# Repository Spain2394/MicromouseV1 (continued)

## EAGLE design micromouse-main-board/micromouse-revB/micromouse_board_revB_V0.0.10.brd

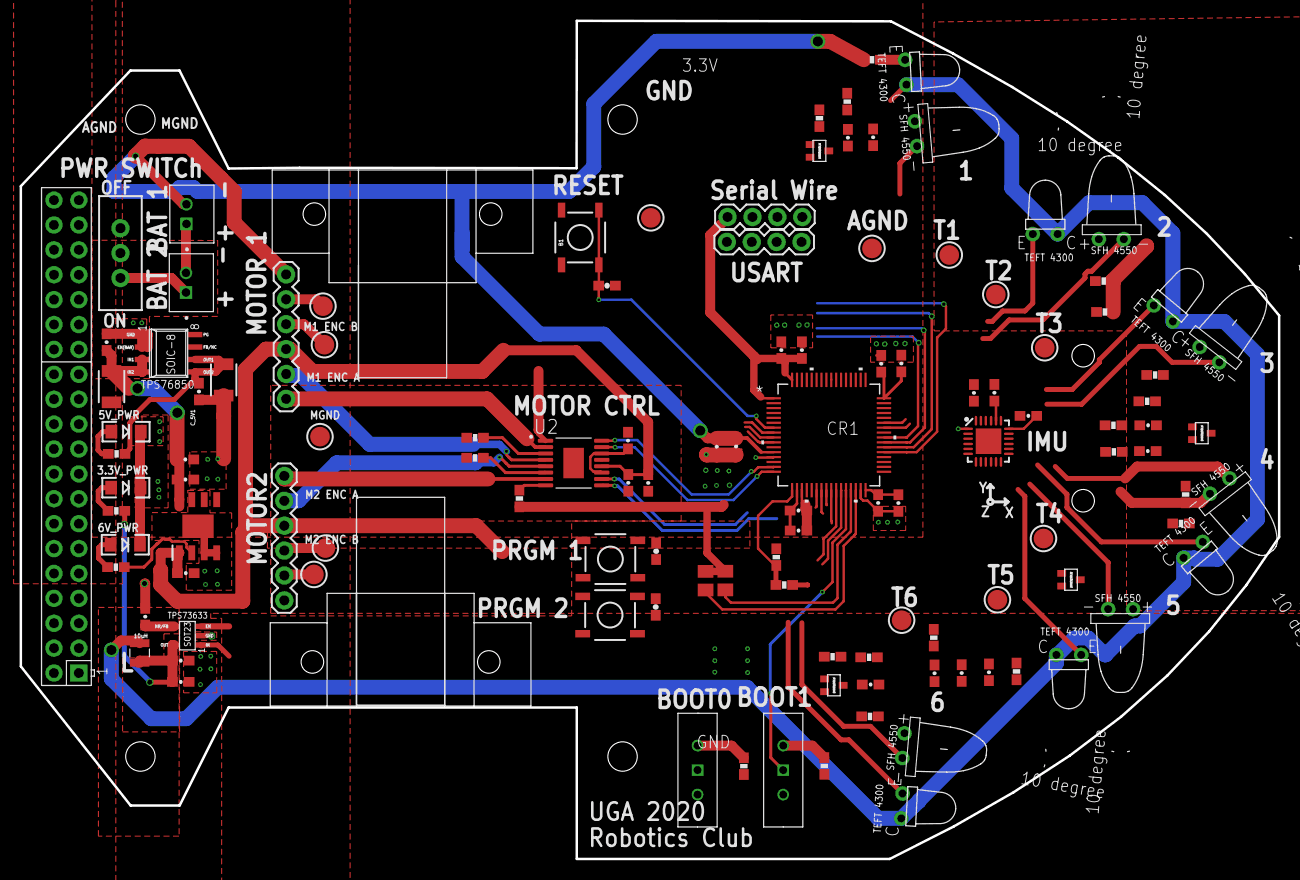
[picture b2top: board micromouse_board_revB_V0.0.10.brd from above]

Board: 2 copper layers, 128.4 x 85.5 mm, 119 parts (0 on the bottom side), 72 nets.

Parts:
3.3V_PWR, 5V_PWR, 6V_PWR: green; LED-1206
B1, B2, B3: TACTILE-SWITCH-SMD
C1: 10nF; 0603-CAP
C2, C18, C21, C23: 4.7uF; 0603-CAP
C4, C7, C17, C22: 0.1uF; 0603-CAP
C8: 1uF; 0603-CAP
CR1: STM32F103RET6; LQFP-64
C_3.3V1, C_3.3V6: 10uF; 0603-CAP
C_3.3V2, C_3.3V7, C_5V1: 0.1uF; 0603-CAP
C_3.3V5: 1uF; 0603-CAP
C_5V2: 47uF; 1210
C_BAT1: 0.1uF; 0603-CAP
C_BAT2: 47uF; 1210
C_D: 0.1uF; 0603-CAP
C_D1: 10uF; 0603-CAP
C_D2: 2.2uF; 0603-CAP
C_ELF1: 4.7uF; 0603-CAP
C_ELF2: 0.1uF; 0603-CAP
C_EM_D1: 4.7uF; 0603-CAP
C_EM_D2: 0.1uF; 0603-CAP
C_ERF1: 4.7uF; 0603-CAP
C_ERF2: 0.1uF; 0603-CAP
C_E_H1: 4.7uF; 0603-CAP
C_E_H2: 0.1uF; 0603-CAP
C_NR: 0.1uF; 0603-CAP
C_NRST, C_NRST1, C_NRST2: 0.1uF; 0603-CAP
IMU_C1, IMU_C2: 0.1uF; 0603-CAP
IMU_C3: 2.2nF; 0603-CAP
J1, J4: 1X04
J2, J3: JST_PH; JST_B2B-PH-K-S(LF)(SN)
L1: 10uH; 1007
LEFT_FRONT_EMITTER: EMITTER
NMOS1, NMOS2, NMOS3, NMOS4: DMN3150LW
R4, R5: 4.6k; M0805
REC_LF: RECEIVER
R_B1, R_B2: 47k; 0603-RES
R_ED1, R_ED2: 5.6; 0603-RES
R_ED_PD: 47k; 0603-RES
R_EH1, R_EH2: 5.6; 0603-RES
R_EH_PD: 47k; 0603-RES
R_ELF: 10; 0603-RES
R_ELF_PD: 47k; 0603-RES
R_ERF: 30; 0603-RES
R_ERF_PD: 47k; 0603-RES
R_PWR1, R_PWR3, R_PWR4: 100 Ohm; 0603-RES
R_RLD: 1.8k; 0603-RES
R_RLF: 1.8k; 0603-RES
R_RLH: 1.8k; 0603-RES
R_RRD: 1.8k; 0603-RES
R_RRF: 1.8k; 0603-RES
R_RRH: 1.8k; 0603-RES
R_VM1: 70k; 0603-RES
R_VM2: 40k; 0603-RES
R_VM3, R_VM4: 500m; 0603-RES
R_VM5: 10k; 0603-RES
S2: SWITCH-SPDT
T1, T2, T3, T4, T5, T6: TESTPOINT_ROUND_2MM
TP7, TP8, TP9, TP10, TP11, TP12, TP13: TESTPOINT_ROUND_2MM
U2: DRV8848PWPR; SOP65P640X120-17N
U6: MPU-6000; QFN-24-EP
U$3: TPS73633(SOT-23)
U$4: TPS76850(SOIC-8)
U$5, U$6: 6P_HEADER
U$7, U$8, U$9, U$20, U$21: RECEIVER
U$11, U$13, U$17, U$18, U$19: EMITTER
U$14, U$15: SPARKFUN-SPDT; SPDT
U$16, U$22: SPLITTER
U$23: BD60HC5WEFJ; SOIC127P600X100-9N
X1: RASPI_GPIO_B+#_PIN; RASPI_GPIO_B+_PIN

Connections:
3.3V: C2.2, C4.2, C7.1, C17.1, C18.2, C21.2, C22.1, C23.2, CR1.1, CR1.19, CR1.32, CR1.48, CR1.64, C_3.3V1.1, C_3.3V2.1, J1.4, J4.2, L1.1, R4.2, R5.2, R_B1.2, R_B2.2, R_PWR4.2, R_VM5.2, U2.1, U$3.OUT, X1.1, X1.17
5V: C_5V1.1, C_5V2.1, C_ELF1.1, C_ELF2.1, C_EM_D1.1, C_EM_D2.1, C_ERF1.1, C_ERF2.1, C_E_H1.1, C_E_H2.1, LEFT_FRONT_EMITTER.+, R_PWR1.2, U$3.EN, U$3.IN, U$4.OUT1, U$4.OUT2, U$11.+, U$13.+, U$18.+, X1.2, X1.4
6V: C_3.3V5.1, C_D.1, C_D1.1, U2.12, U$5.3, U$6.3, U$23.1
6V_S: R_PWR3.2, U$23.2
A3.3V: C1.2, C8.2, CR1.13, IMU_C2.1, L1.2, REC_LF.C, U6.13, U$7.C, U$8.C, U$9.C, U$20.C, U$21.C
AGND: C1.1, C8.1, CR1.12, IMU_C1.2, IMU_C2.2, IMU_C3.2, R_RLD.1, R_RLF.1, R_RLH.1, R_RRD.1, R_RRF.1, R_RRH.1, R_VM2.1, TP12.P$1, U6.1, U6.11, U6.18, U$22.2
BOOT0: CR1.60, U$14.P$2
BOOT1: CR1.28, U$15.P$2
BRIDGE_A_1: CR1.15, U2.16
BRIDGE_A_2: CR1.16, U2.15
BRIDGE_B_1: CR1.26, U2.9
BRIDGE_B_2: CR1.27, U2.10
D2_EM: R_ED1.2, R_ED2.2, U$17.-
D_EM: U$11.-, U$17.+
EM_D: CR1.59, NMOS2.G, R_ED_PD.2
EM_H: CR1.62, NMOS4.G, R_EH_PD.2
EM_LF: CR1.58, NMOS1.G, R_ELF_PD.2
EM_RF: CR1.61, NMOS3.G, R_ERF_PD.2
GND: 3.3V_PWR.C, 5V_PWR.C, 6V_PWR.C, B1.1, B1.2, B2.1, B2.2, B3.1, B3.2, C2.1, C4.1, C7.2, C17.2, C18.1, C21.1, C22.2, C23.1, CR1.18, CR1.31, CR1.47, CR1.63, C_3.3V1.2, C_3.3V2.2, C_3.3V5.2, C_3.3V6.2, C_3.3V7.2, C_5V1.2, C_5V2.2, C_BAT1.2, C_BAT2.2, C_ELF1.2, C_ELF2.2, C_EM_D1.2, C_EM_D2.2, C_ERF1.2, C_ERF2.2, C_E_H1.2, C_E_H2.2, C_NR.2, C_NRST.2, C_NRST1.2, C_NRST2.2, J1.1, J2.2, J4.1, NMOS1.S, NMOS2.S, NMOS3.S, NMOS4.S, R_ED_PD.1, R_EH_PD.1, R_ELF_PD.1, R_ERF_PD.1, TP13.P$1, U$3.GND, U$4.EN(BAR), U$4.GND, U$14.P$3, U$15.P$3, U$16.1, U$22.1, U$23.3, U$23.4, U$23.6, U$23.7, U$23.9, X1.6, X1.9, X1.14, X1.20, X1.25, X1.30, X1.34, X1.39
H2_EM: R_EH1.2, R_EH2.2, U$19.-
H_EM: U$18.-, U$19.+
I2C_SCL: CR1.29, R4.1, U6.23
I2C_SDA: CR1.30, R5.1, U6.24
INT: CR1.56, U6.12
LF_EM: LEFT_FRONT_EMITTER.-, R_ELF.2
M1_A: U2.2, U$6.1
M1_B: U2.4, U$6.2
M1_ENC_A: CR1.37, TP7.P$1, U$6.4
M1_ENC_B: CR1.38, TP8.P$1, U$6.5
M2_A: U2.7, U$5.1
M2_B: U2.5, U$5.2
M2_ENC_A: CR1.40, TP9.P$1, U$5.4
M2_ENC_B: CR1.39, TP10.P$1, U$5.5
MGND: C_D.2, C_D1.2, C_D2.2, R_VM3.2, R_VM4.2, TP11.P$1, U2.13, U$5.6, U$6.6, U$16.2
unnamed: 3.3V_PWR.A, R_PWR4.1
unnamed: R_VM4.1, U2.3
unnamed: J2.1, J3.2
unnamed: R_B2.1, U$15.P$1
unnamed: NMOS3.D, R_ERF.1
unnamed: R_B1.1, U$14.P$1
unnamed: NMOS1.D, R_ELF.1
unnamed: R_VM3.1, U2.6
unnamed: 6V_PWR.A, R_PWR3.1
unnamed: C_D2.1, U2.11, U2.14
unnamed: 5V_PWR.A, R_PWR1.1
unnamed: NMOS2.D, R_ED1.1, R_ED2.1
unnamed: NMOS4.D, R_EH1.1, R_EH2.1
unnamed: C_NR.1, U$3.NR/FB
unnamed: IMU_C1.1, U6.10
unnamed: IMU_C3.1, U6.20
NFAULT: CR1.54, R_VM5.1, U2.8
PRGM_1: B2.3, B2.4, CR1.10, C_NRST1.1
PRGM_2: B3.3, B3.4, CR1.11, C_NRST2.1
REC_LD: CR1.23, R_RLD.2, T3.P$1, U$7.E
REC_LF: CR1.22, REC_LF.E, R_RLF.2, T1.P$1
REC_LH: CR1.8, R_RLH.2, T2.P$1, U$21.E
REC_RD: CR1.24, R_RRD.2, T4.P$1, U$8.E
REC_RF: CR1.25, R_RRF.2, T6.P$1, U$9.E
REC_RH: CR1.9, R_RRH.2, T5.P$1, U$20.E
RESET: B1.3, B1.4, CR1.7, C_NRST.1
RF_EM: R_ERF.2, U$13.-
SPI2_MISO: CR1.35, X1.21
SPI2_MOSI: CR1.36, X1.19
SPI2_NSS: CR1.33, X1.24
SPI2_SCK: CR1.34, X1.23
SWCLK: CR1.49, J1.2
SWDIO: CR1.46, J1.3
USART1_RX: CR1.43, J4.4, X1.8
USART1_TX: CR1.42, J4.3, X1.10
VBAT_POWER: J3.1, S2.3
VBAT_SENSE: CR1.17, R_VM1.1, R_VM2.2
V_BATT: C_3.3V6.1, C_3.3V7.1, C_BAT1.1, C_BAT2.1, R_VM1.2, S2.2, U$4.IN1, U$4.IN2, U$23.5, U$23.8

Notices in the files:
parts and their libraries:
SparkFun-Retired: Licensing:Creative Commons ShareAlike 4.0 International - https://creativecommons.org/licenses/by-sa/4.0
SparkFun: Licensing: CC v3.0 Share-Alike You are welcome to use this library for commercial purposes.
